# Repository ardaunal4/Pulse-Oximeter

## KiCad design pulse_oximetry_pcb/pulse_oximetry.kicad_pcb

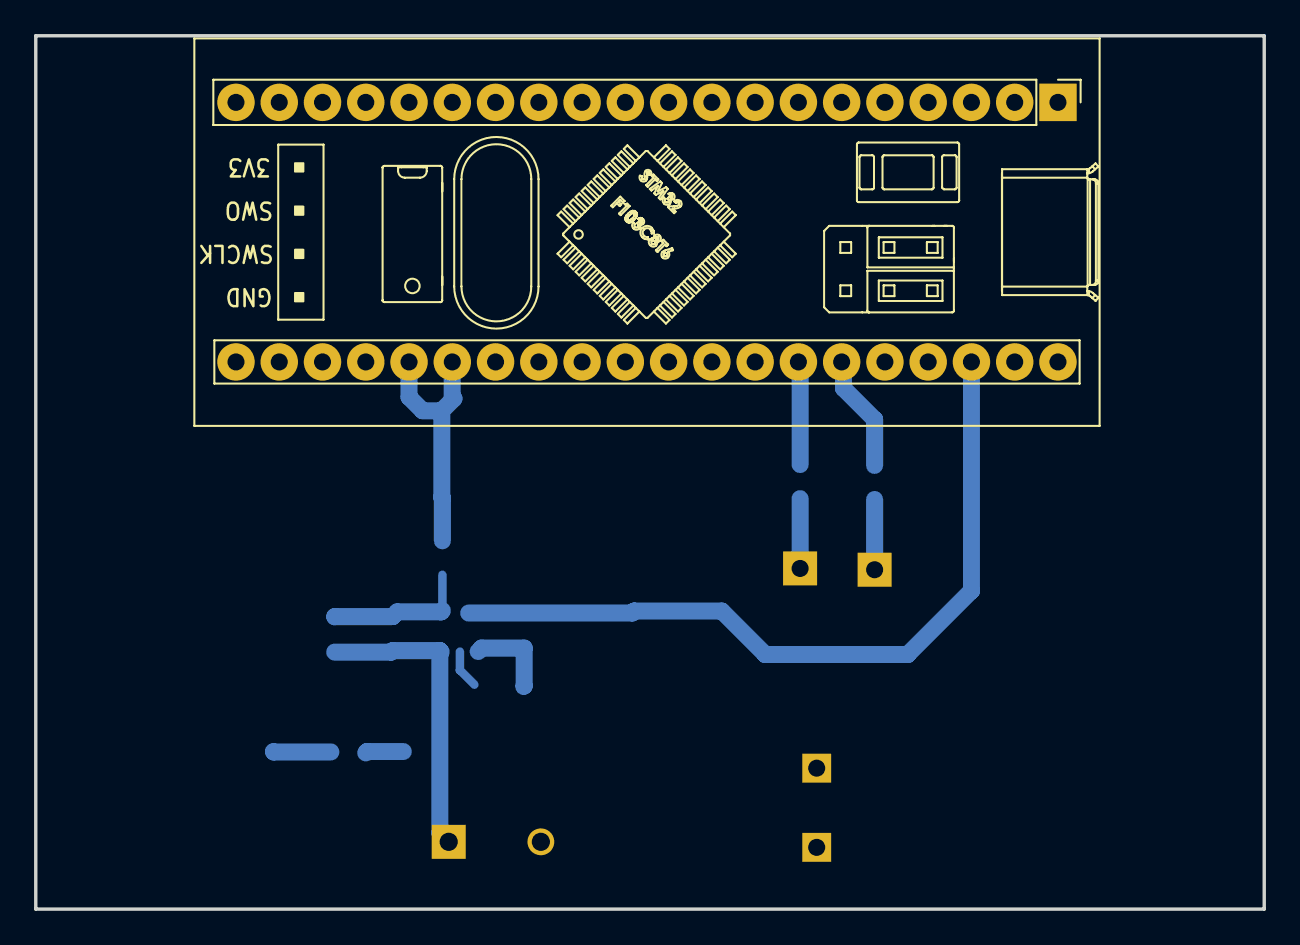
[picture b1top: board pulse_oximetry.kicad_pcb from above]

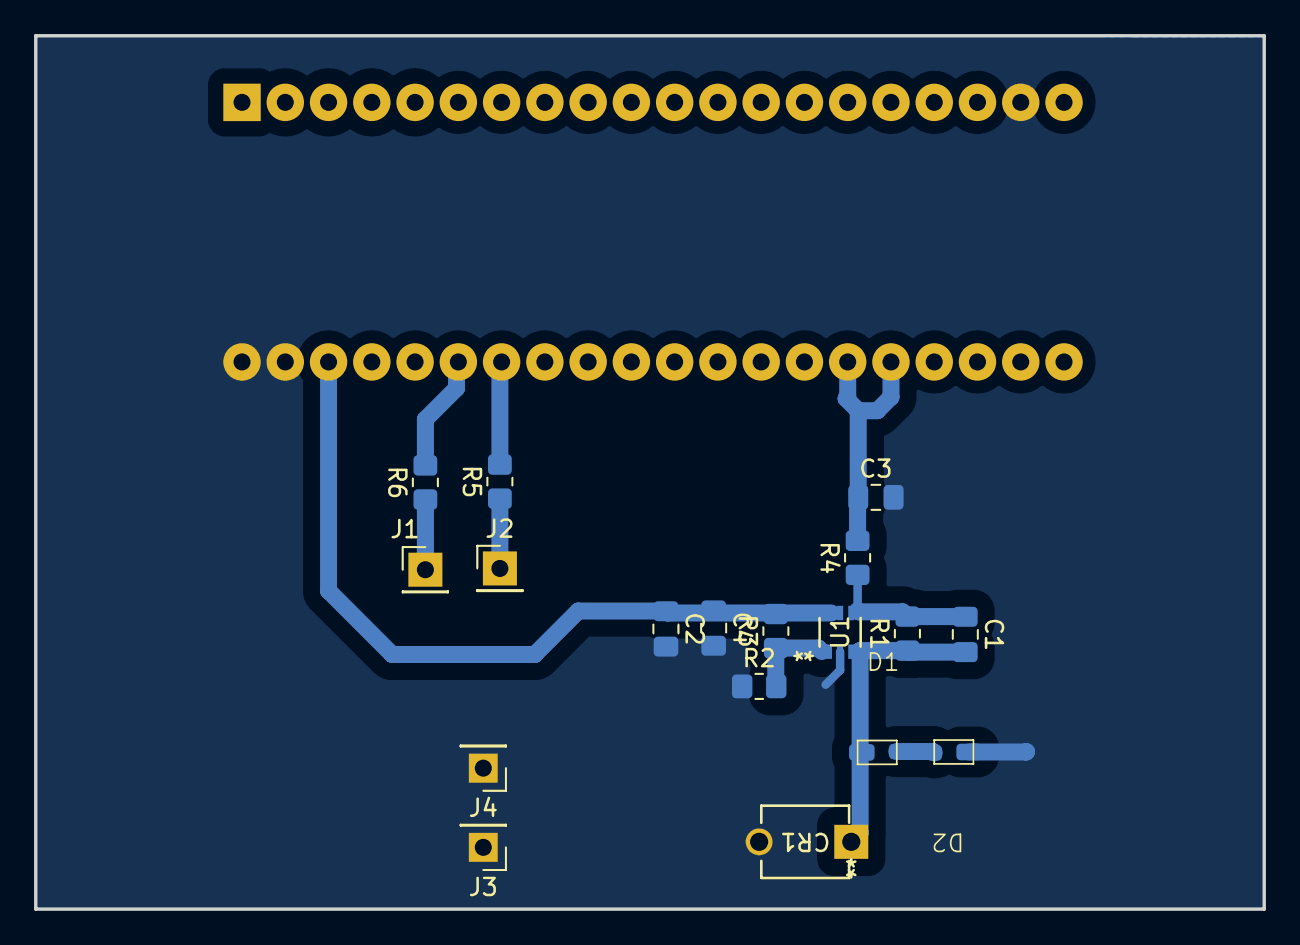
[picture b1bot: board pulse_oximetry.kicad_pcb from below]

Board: 2 copper layers, 72.1 x 51.3 mm, 19 parts (18 on the bottom side), 11 nets.

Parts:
C1: 6.8pF; C_0805_2012Metric_Pad1.18x1.45mm_HandSolder
C2: 100nF; C_0805_2012Metric_Pad1.18x1.45mm_HandSolder
C3: 1nF; C_0805_2012Metric_Pad1.18x1.45mm_HandSolder
C4: 1uF; C_0805_2012Metric_Pad1.18x1.45mm_HandSolder
CR1: BPW34; LED_BPW34_VIS
D1, D2: mse1pghm3; MSE1PPGHM3
J1, J2, J3, J4: Conn_01x01_Pin; PinHeader_1x01_P2.54mm_Vertical
R1, R3: 32k; R_0805_2012Metric_Pad1.20x1.40mm_HandSolder
R2: 1k; R_0805_2012Metric_Pad1.20x1.40mm_HandSolder
R4: 10k; R_0805_2012Metric_Pad1.20x1.40mm_HandSolder
R5, R6: 110; R_0805_2012Metric_Pad1.20x1.40mm_HandSolder
U1: LMV601MG/NOPB; DCK6_TEX
U2: YAAJ_BluePill; YAAJ_BluePill_1

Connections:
+3V3: C2.1, C4.1, R3.2, U1.5 (*SHDN), U1.6 (V+), U2.38 (3V3)
/ampOUT: C3.1, R4.2, U2.25 (PA0), U2.26 (PA1)
GND: C2.2, C3.2, C4.2, CR1.2, J3.1, J4.1, R2.1, U1.2 (GND), U2.19 (GND), U2.39 (GND), U2.40 (GND)
unnamed: D1.1 (A), D1.2 (A), D2.1 (A), D2.2 (A)
unnamed: C1.2, CR1.1, R1.1, U1.3 (-IN)
unnamed: J1.1, R6.1
unnamed: J2.1, R5.1
unnamed: R2.2, R3.1, U1.1 (+IN)
unnamed: C1.1, R1.2, R4.1, U1.4 (OUT)
unnamed: R5.2, U2.34 (PB1)
unnamed: R6.2, U2.35 (PB10)

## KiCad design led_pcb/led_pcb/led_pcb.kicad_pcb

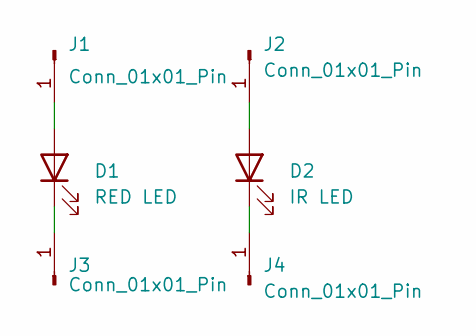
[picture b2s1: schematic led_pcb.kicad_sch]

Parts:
D1: RED LED; LED_D3.0mm
D2: IR LED; LED_D3.0mm
J1, J2, J3, J4: Conn_01x01_Pin; PinHeader_1x01_P2.54mm_Vertical

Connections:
unnamed: D1.2 (A), J1.1
unnamed: D1.1 (K), J3.1
unnamed: D2.2 (A), J2.1
unnamed: D2.1 (K), J4.1

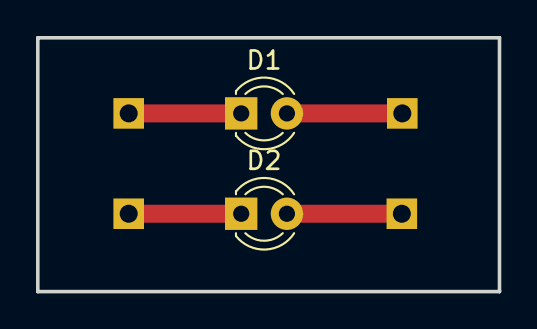
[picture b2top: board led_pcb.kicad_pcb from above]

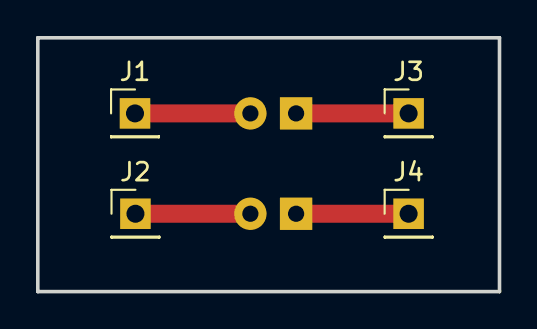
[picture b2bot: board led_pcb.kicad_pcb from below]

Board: 2 copper layers, 25.7 x 14.1 mm, 6 parts (4 on the bottom side), 4 nets.
